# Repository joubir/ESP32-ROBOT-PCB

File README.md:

# ESP32-ROBOT-PCB
An all in one Robot PCB base on ESP32 (command robot , line follower , obstacle robot)

the file include two PCB (panelized) controlle pcb and line follower sensor pcb .
i din't print the the PCB yet put i will make you know when i do .

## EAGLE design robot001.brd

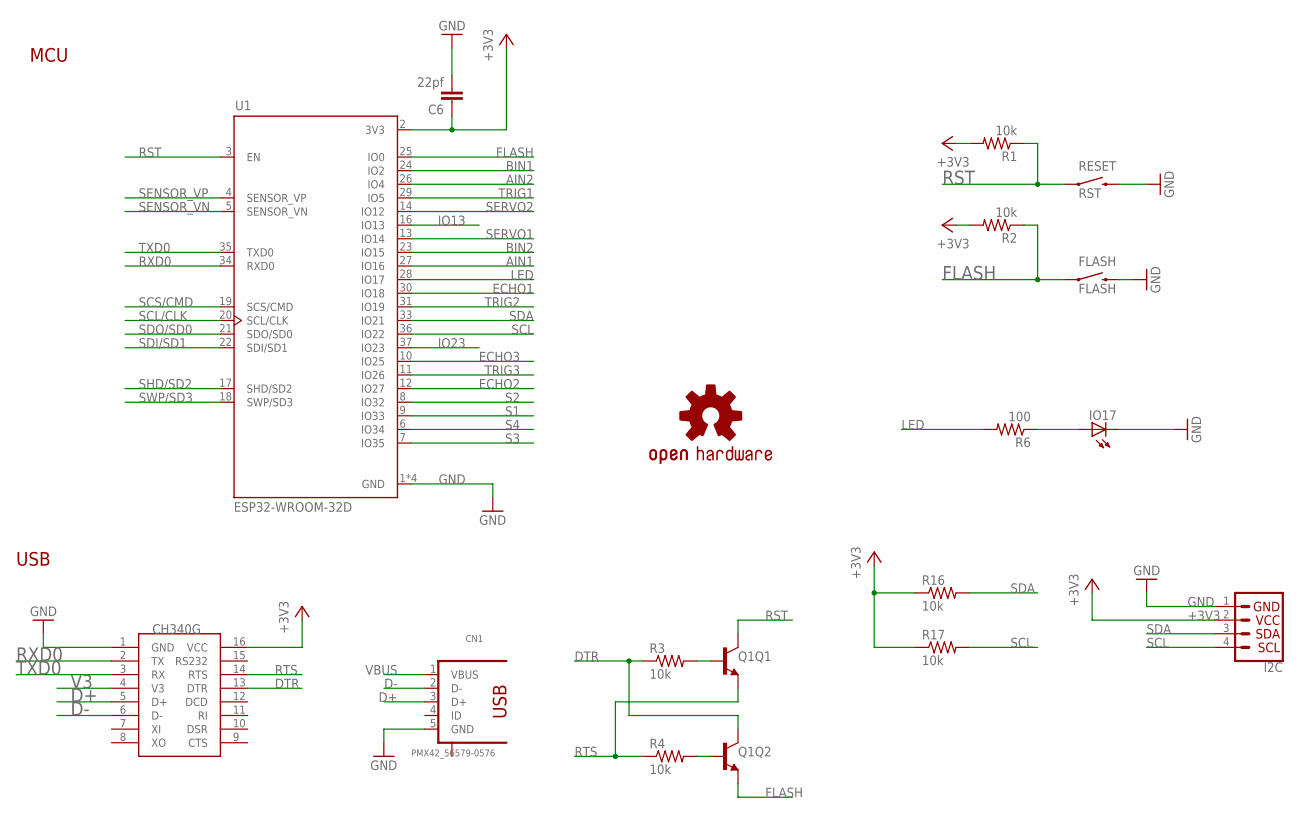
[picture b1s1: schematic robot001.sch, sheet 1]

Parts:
C6: 22pf; C0402
CN1: PMX42_56579-0576
FLASH: FLASH; TACTILE-SWITCH-1101NE
I2C: I2C_STANDARD; 1X04
IO17: LEDCHIPLED_1206; CHIPLED_1206
LOGO1: OSHW-LOGOS; OSHW-LOGO-S
Q1: TRANS_NPN_DUAL-MBT3904DW1T1; SC70-6
R1, R2, R3, R4, R16, R17: 10k; R0402
R6: 100; R0402
RESET: RST; TACTILE-SWITCH-1101NE
U1: ESP32-WROOM-32D; MODULE_ESP32-WROOM-32D
U$1: CH340G; SOIC16

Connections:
+3V3: C6.1, I2C.2, R1.2, R2.2, R16.1, R17.1, U1.2 (3V3), U$1.16 (VCC); also elsewhere on the board
AIN1: U1.27 (IO16); also elsewhere on the board
AIN2: U1.26 (IO4); also elsewhere on the board
BIN1: U1.24 (IO2); also elsewhere on the board
BIN2: U1.23 (IO15); also elsewhere on the board
D+: CN1.3 (D+), U$1.5 (D+)
D-: CN1.2 (D-), U$1.6 (D-)
DTR: Q1.6 (C), R3.1, U$1.13 (DTR)
ECHO1: U1.30 (IO18); also elsewhere on the board
ECHO2: U1.12 (IO27); also elsewhere on the board
ECHO3: U1.10 (IO25); also elsewhere on the board
FLASH: FLASH.1, Q1.1 (E), R2.1, U1.25 (IO0)
GND: C6.2, CN1.5 (GND), FLASH.2, I2C.1, IO17.C, RESET.2, U1.1 (GND), U1.15 (GND), U1.38 (GND), U1.39 (GND), U$1.1 (GND); also elsewhere on the board
IO13: U1.16 (IO13)
IO23: U1.37 (IO23)
LED: R6.2, U1.28 (IO17)
unnamed: Q1.5 (B), R3.2
unnamed: Q1.2 (B), R4.2
unnamed: IO17.A, R6.1
RST: Q1.3 (C), R1.1, RESET.1, U1.3 (EN)
RTS: Q1.4 (E), R4.1, U$1.14 (RTS)
RXD0: U1.34 (RXD0), U$1.2 (TX)
S1: U1.9 (IO33); also elsewhere on the board
S2: U1.8 (IO32); also elsewhere on the board
S3: U1.7 (IO35); also elsewhere on the board
S4: U1.6 (IO34); also elsewhere on the board
SCL: I2C.4, R17.2, U1.36 (IO22)
SCL/CLK: U1.20 (SCL/CLK)
SCS/CMD: U1.19 (SCS/CMD)
SDA: I2C.3, R16.2, U1.33 (IO21)
SDI/SD1: U1.22 (SDI/SD1)
SDO/SD0: U1.21 (SDO/SD0)
SENSOR_VN: U1.5 (SENSOR_VN)
SENSOR_VP: U1.4 (SENSOR_VP)
SERVO1: U1.13 (IO14); also elsewhere on the board
SERVO2: U1.14 (IO12); also elsewhere on the board
SHD/SD2: U1.17 (SHD/SD2)
SWP/SD3: U1.18 (SWP/SD3)
TRIG1: U1.29 (IO5); also elsewhere on the board
TRIG2: U1.31 (IO19); also elsewhere on the board
TRIG3: U1.11 (IO26); also elsewhere on the board
TXD0: U1.35 (TXD0), U$1.3 (RX)
V3: U$1.4 (V3)
VBUS: CN1.1 (VBUS); also elsewhere on the board

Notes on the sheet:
USB
MCU

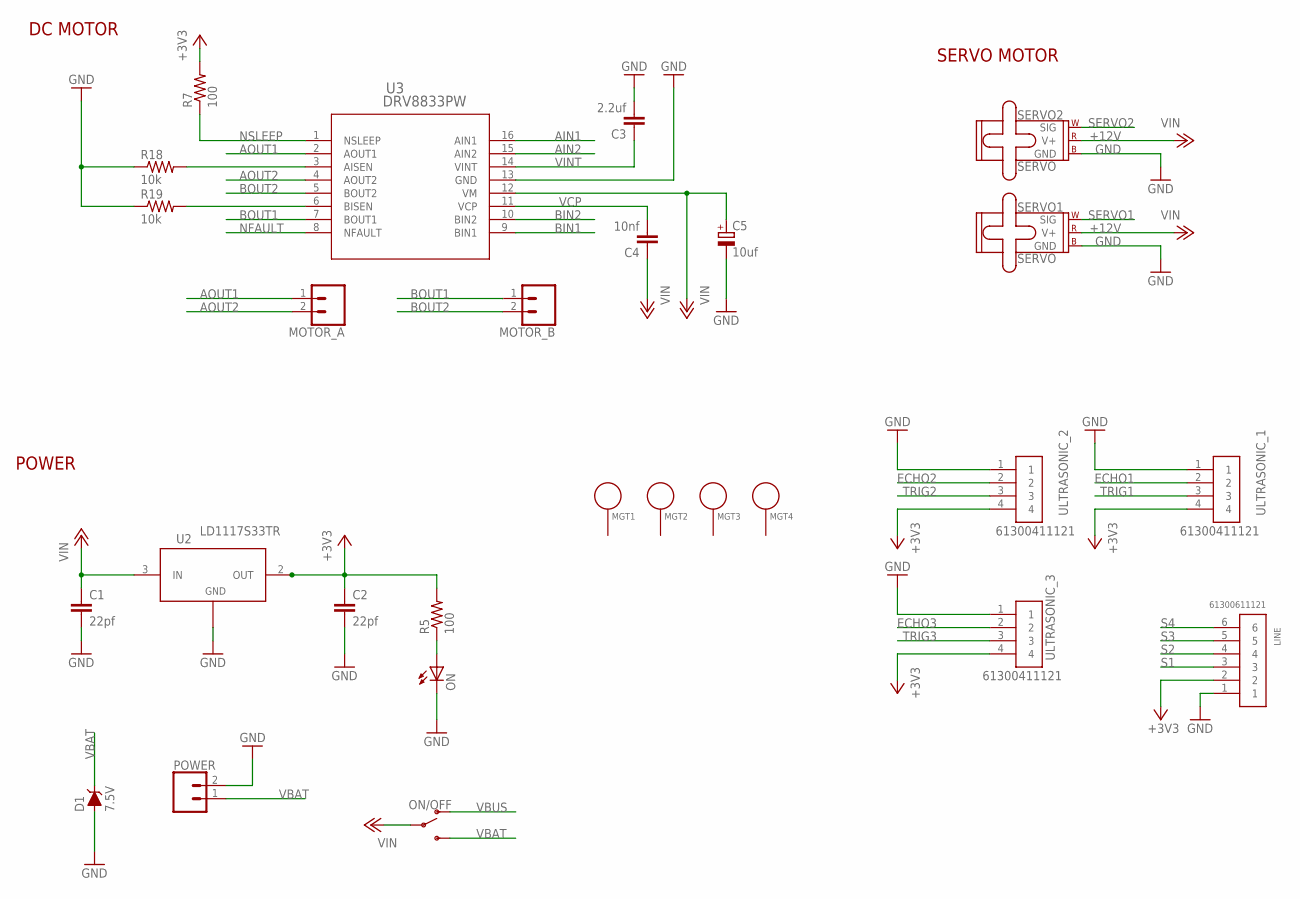
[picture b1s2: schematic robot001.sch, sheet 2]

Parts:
C1, C2: 22pf; C0402
C3: 2.2uf; C0402
C4: 10nf; C0402
C5: 10uf; PANASONIC_B
D1: 7.5V; SOD-323
LINE: 61300611121
MGT1, MGT2, MGT3, MGT4: BEAGLEBONEBLACK_MOUNTING_HOLE
MOTOR_A: CONN_02; 1X02
MOTOR_B: CONN_02; 1X02
ON: LEDCHIPLED_1206; CHIPLED_1206
ON/OFF: SWITCH-SPDT-SMD-AYZ0202; SWITCH_DPDT_SMD_AYZ0202
POWER: CONN_02; 1X02
R5, R7: 100; R0402
R18, R19: 10k; R0402
SERVO1, SERVO2: SERVO; 1X03
U2: LD1117S33TR; SOT-223
U3: DRV8833PW; PW16
ULTRASONIC_1, ULTRASONIC_2, ULTRASONIC_3: 61300411121

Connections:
+3V3: C2.1, LINE.2, R5.2, R7.2, U2.2 (OUT), U2.4, ULTRASONIC_1.4, ULTRASONIC_2.4, ULTRASONIC_3.4; also elsewhere on the board
+12V: C1.1, C4.1, C5.+, ON/OFF.2, SERVO1.2 (V+), SERVO2.2 (V+), U2.3 (IN), U3.12 (VM)
AIN1: U3.16 (AIN1); also elsewhere on the board
AIN2: U3.15 (AIN2); also elsewhere on the board
AOUT1: MOTOR_A.1, U3.2 (AOUT1)
AOUT2: MOTOR_A.2, U3.4 (AOUT2)
BIN1: U3.9 (BIN1); also elsewhere on the board
BIN2: U3.10 (BIN2); also elsewhere on the board
BOUT1: MOTOR_B.1, U3.7 (BOUT1)
BOUT2: MOTOR_B.2, U3.5 (BOUT2)
ECHO1: ULTRASONIC_1.2; also elsewhere on the board
ECHO2: ULTRASONIC_2.2; also elsewhere on the board
ECHO3: ULTRASONIC_3.2; also elsewhere on the board
GND: C1.2, C2.2, C3.2, C5.-, D1.A, LINE.1, ON.C, POWER.2, R18.1, R19.1, SERVO1.3 (GND), SERVO2.3 (GND), U2.1 (ADJ/GND), U3.13 (GND), ULTRASONIC_1.1, ULTRASONIC_2.1, ULTRASONIC_3.1; also elsewhere on the board
unnamed: ON.A, R5.1
unnamed: R18.2, U3.3 (AISEN)
unnamed: R19.2, U3.6 (BISEN)
NFAULT: U3.8 (NFAULT)
NSLEEP: R7.1, U3.1 (NSLEEP)
S1: LINE.3; also elsewhere on the board
S2: LINE.4; also elsewhere on the board
S3: LINE.5; also elsewhere on the board
S4: LINE.6; also elsewhere on the board
SERVO1: SERVO1.1 (SIG); also elsewhere on the board
SERVO2: SERVO2.1 (SIG); also elsewhere on the board
TRIG1: ULTRASONIC_1.3; also elsewhere on the board
TRIG2: ULTRASONIC_2.3; also elsewhere on the board
TRIG3: ULTRASONIC_3.3; also elsewhere on the board
VBAT: D1.C, ON/OFF.3 (S), POWER.1
VBUS: ON/OFF.1 (O); also elsewhere on the board
VCP: C4.2, U3.11 (VCP)
VINT: C3.1, U3.14 (VINT)

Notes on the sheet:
DC MOTOR
SERVO MOTOR
POWER

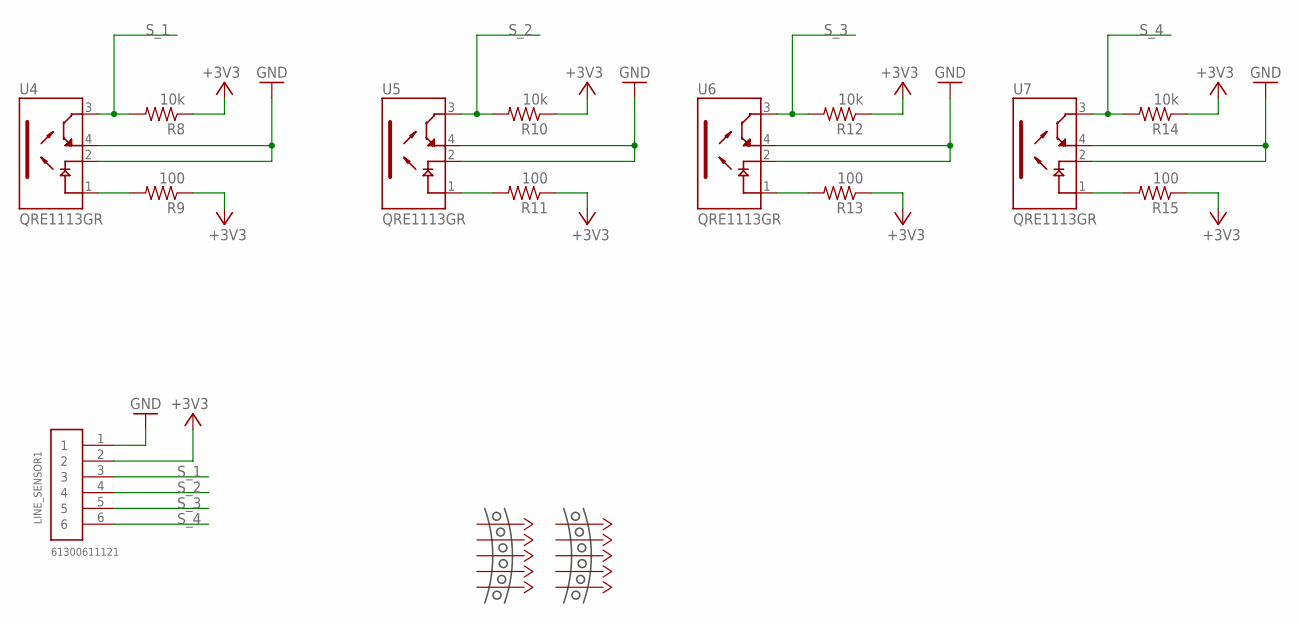
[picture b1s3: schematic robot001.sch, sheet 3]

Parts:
LINE_SENSOR1: 61300611121
R8, R10, R12, R14: 10k; R0402
R9, R11, R13, R15: 100; R0402
U4, U5, U6, U7: QRE1113GR; SOIC180P460X187-4N
U$2, U$3: MOUSE-BITES-5

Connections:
+3V3: LINE_SENSOR1.2, R8.1, R9.1, R10.1, R11.1, R12.1, R13.1, R14.1, R15.1; also elsewhere on the board
GND: LINE_SENSOR1.1, U4.2 (C), U4.4 (ET), U5.2 (C), U5.4 (ET), U6.2 (C), U6.4 (ET), U7.2 (C), U7.4 (ET); also elsewhere on the board
unnamed: R11.2, U5.1 (A)
unnamed: R9.2, U4.1 (A)
unnamed: R13.2, U6.1 (A)
unnamed: R15.2, U7.1 (A)
S_1: LINE_SENSOR1.3, R8.2, U4.3 (CT)
S_2: LINE_SENSOR1.4, R10.2, U5.3 (CT)
S_3: LINE_SENSOR1.5, R12.2, U6.3 (CT)
S_4: LINE_SENSOR1.6, R14.2, U7.3 (CT)

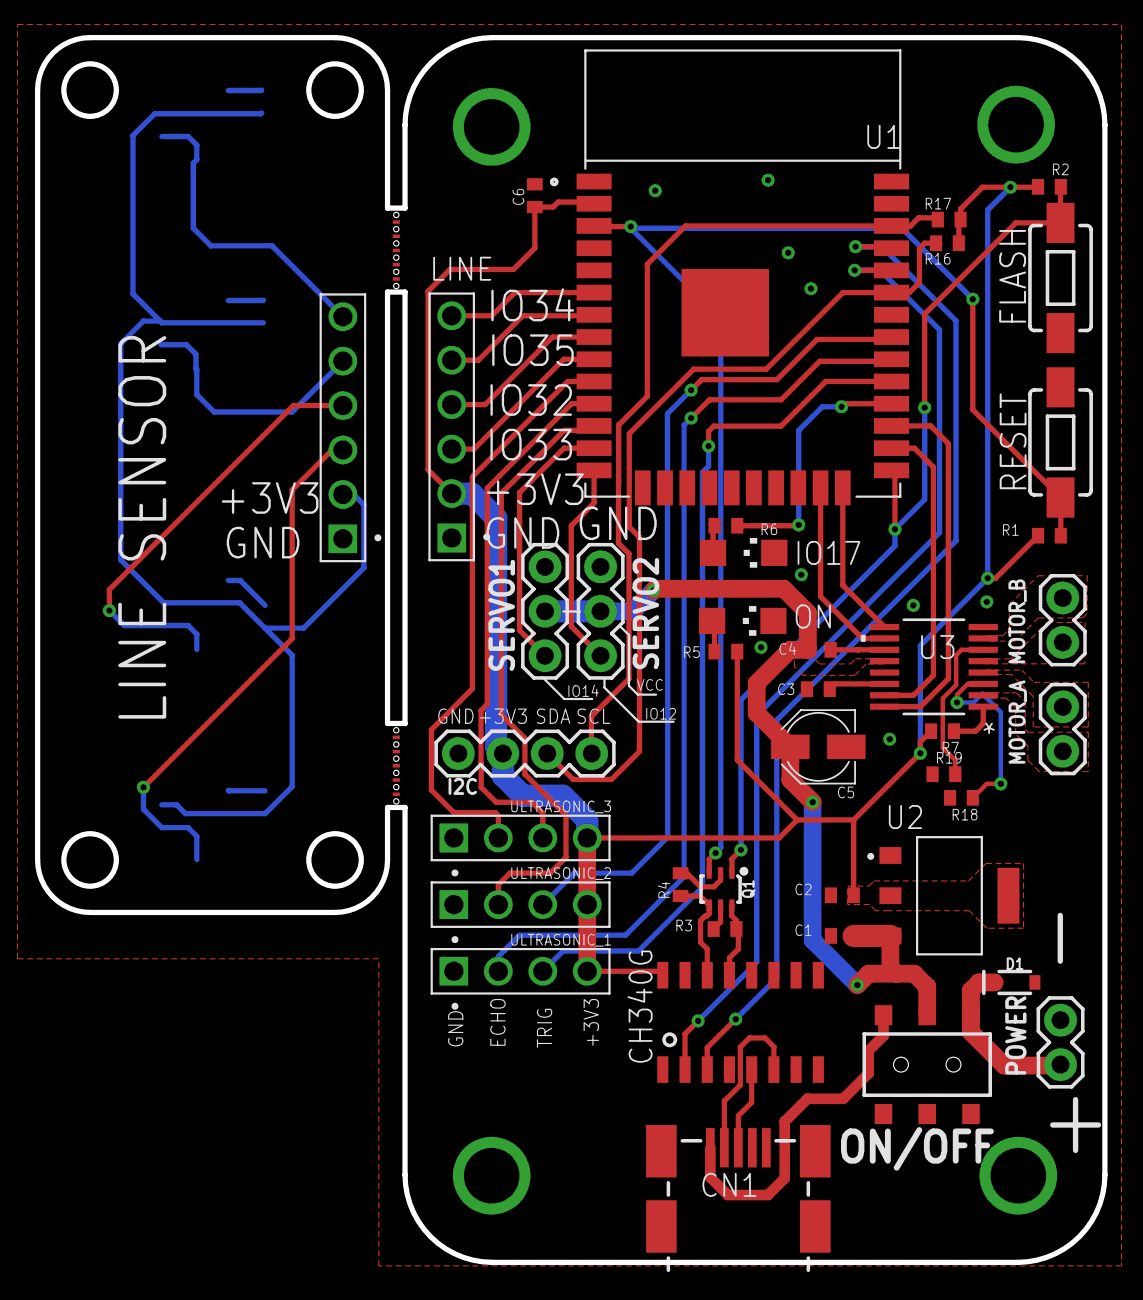
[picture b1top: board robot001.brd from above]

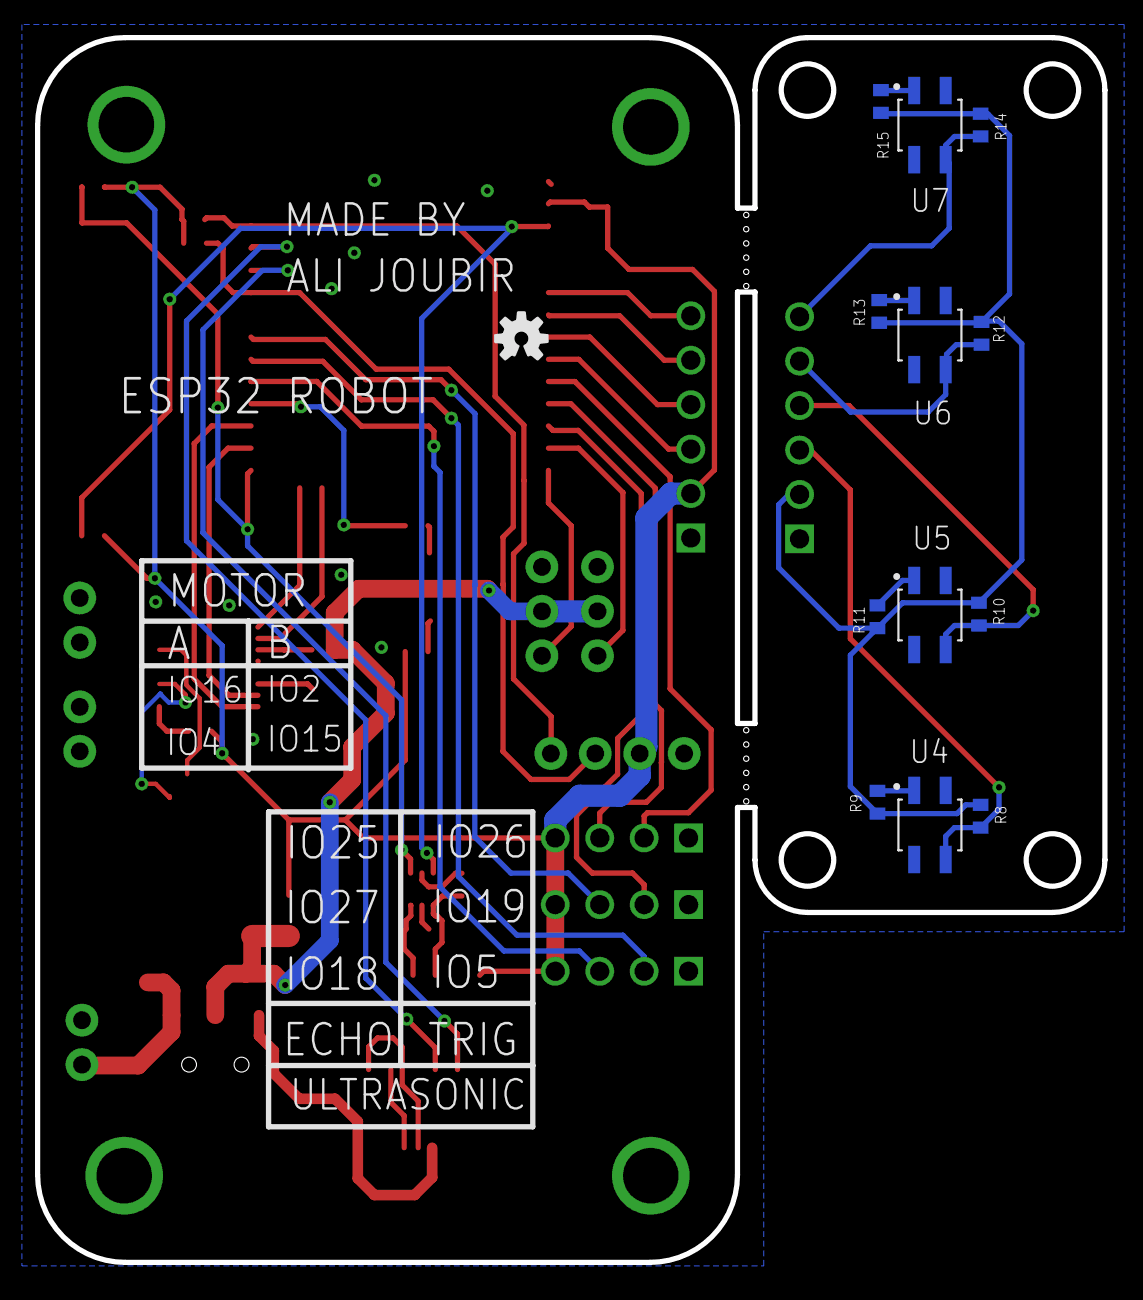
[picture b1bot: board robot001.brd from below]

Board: 2 copper layers, 61.0 x 70.0 mm, 59 parts (14 on the bottom side), 53 nets.

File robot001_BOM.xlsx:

Qty | Value | Device | Package | Parts | Description
3 |  | CONN_02 | 1X02 | MOTOR_A, MOTOR_B, POWER | Multi connection point. Often used as Generic Header-pin footprint for 0.1 inch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
1 |  | I2C_STANDARD | 1X04 | I2C | SparkFun I2C Standard Pinout Header
2 |  | LEDCHIPLED_1206 | CHIPLED_1206 | IO17, ON | LED
1 |  | SWITCH-SPDT-SMD-AYZ0202 | SWITCH_DPDT_SMD_AYZ0202 | ON/OFF | Single Pole, Double Throw (SPDT) Switch
1 |  | TRANS_NPN_DUAL-MBT3904DW1T1 | SC70-6 | Q1 | Dual NPN Transistors in Single Package
7 | 100 | R-US_R0402 | R0402 | R5, R6, R7, R9, R11, R13, R15 | RESISTOR, American symbol
10 | 10k | R-US_R0402 | R0402 | R1, R2, R3, R4, R8, R10, R12, R14, R16, R17 | RESISTOR, American symbol
1 | 10nf | C-EUC0402 | C0402 | C4 | CAPACITOR, European symbol
1 | 10uf | CPOL-EUB | PANASONIC_B | C5 | POLARIZED CAPACITOR, European symbol
1 | 2.2uf | C-EUC0402 | C0402 | C3 | CAPACITOR, European symbol
3 | 22pf | C-EUC0402 | C0402 | C1, C2, C6 | CAPACITOR, European symbol
3 | 61300411121 | 61300411121 | 61300411121 | ULTRASONIC_1, ULTRASONIC_2, ULTRASONIC_3 | CONN HEADER VERT 4POS 2.54MM
2 | 61300611121 | 61300611121 | 61300611121 | LINE, LINE_SENSOR1 | CONN HEADER VERT 6POS 2.54MM
1 | 7.5V | DIODE-ZENER-BZT52C3V6S | SOD-323 | D1 | Zener Diode
4 | BEAGLEBONEBLACK_MOUNTING_HOLE | BEAGLEBONEBLACK_MOUNTING_HOLE | BEAGLEBONEBLACK_MOUNTING_HOLE | MGT1, MGT2, MGT3, MGT4 | Chassis Mounting Hole w/GND connection ability
1 | CH340G | CH340G | SOIC16 | U$1
1 | DRV8833PW | DRV8833PW | PW16 | U3
1 | ESP32-WROOM-32D | ESP32-WROOM-32D | MODULE_ESP32-WROOM-32D | U1 | IC: SoC; GPIO, I2C, I2S, IR, SD, SDIO, SPI, UART; 2.7أ·3.6VDC; 20dBm
1 | FLASH | RS032G05A3SM-SPST-MOMENTARY-SWSMD-1101NE | TACTILE-SWITCH-1101NE | FLASH | 6x3.5mm 2-pin Momentary Switch (Push-button)
1 | LD1117S33TR | LD1117S33TR | SOT-223 | U2 | IC REG LINEAR 3.3V 800MA SOT223
2 | MOUSE-BITES-5 | MOUSE-BITES-5 | MOUSE-BITES-5 | U$2, U$3
1 | OSHW-LOGOS | OSHW-LOGOS | OSHW-LOGO-S | LOGO1 | Open Source Hardware Logo This logo indicates the piece of hardware it is found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
1 | PMX42_56579-0576 | PMX42_56579-0576 | PMX42_56579-0576 | CN1 | USB - OTG, miniUSB Type AB, Molex
4 | QRE1113GR | QRE1113GR | SOIC180P460X187-4N | U4, U5, U6, U7 | QRE1113 Series 30 V 50 mA Miniature Reflective Object Sensor - SMD-4
1 | RST | RS032G05A3SM-SPST-MOMENTARY-SWSMD-1101NE | TACTILE-SWITCH-1101NE | RESET | 6x3.5mm 2-pin Momentary Switch (Push-button)
2 | SERVO | SERVO | 1X03 | SERVO1, SERVO2 | Servo Motor

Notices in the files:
parts and their libraries:
SparkFun-Electromechanical: Licensing: Creative Commons ShareAlike 4.0 International - https://creativecommons.org/licenses/by-sa/4.0
Particle-Devices: Licensing: Designed by Particle.
